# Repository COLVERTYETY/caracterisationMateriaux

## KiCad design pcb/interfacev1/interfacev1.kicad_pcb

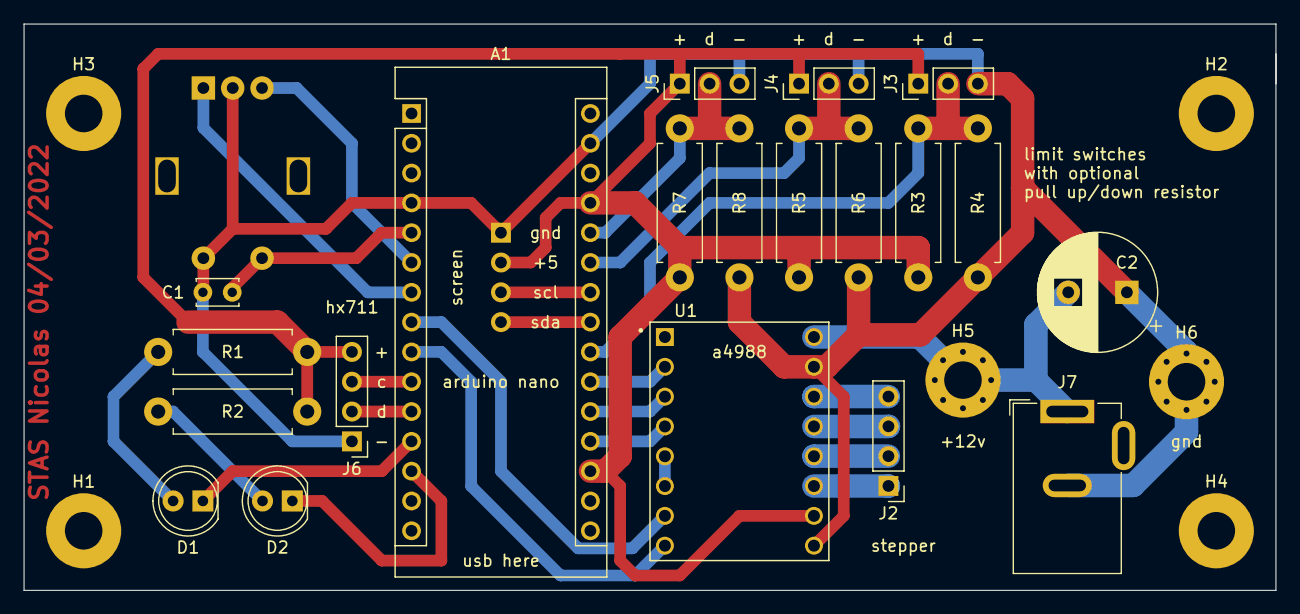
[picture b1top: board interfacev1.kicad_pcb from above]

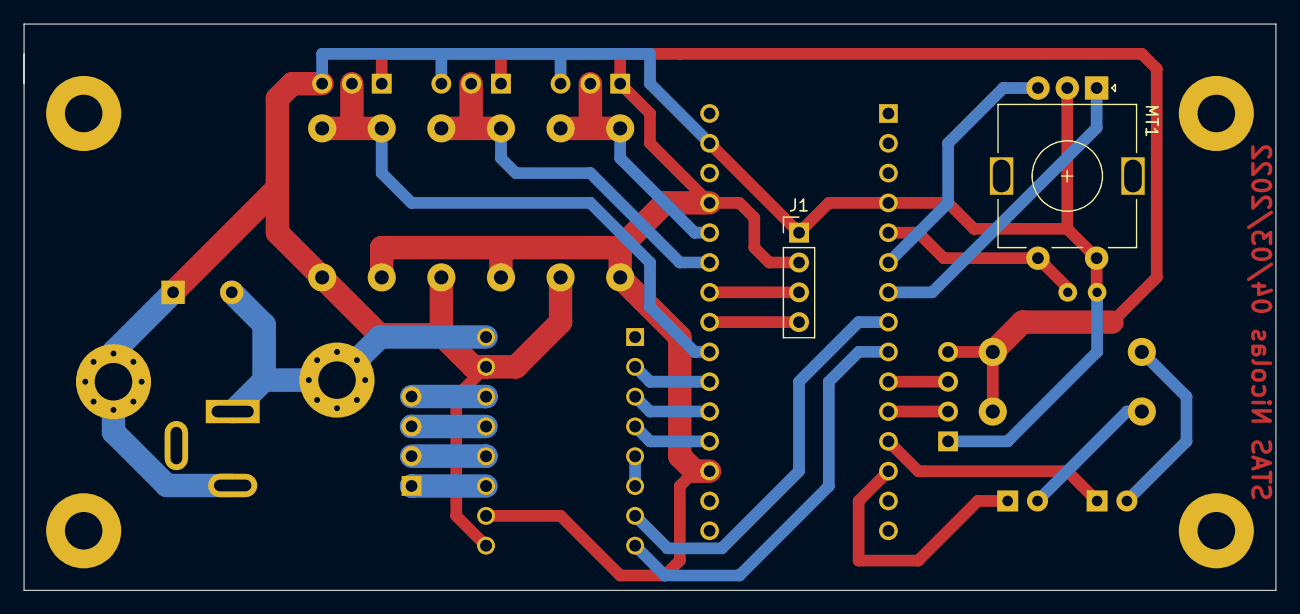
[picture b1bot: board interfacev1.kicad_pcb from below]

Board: 2 copper layers, 106.7 x 48.3 mm, 28 parts (2 on the bottom side), 27 nets.

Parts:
A1: Arduino_Nano_Every; Arduino_Nano
C1: C_Small; C_Disc_D3.4mm_W2.1mm_P2.50mm
C2: C; CP_Radial_D10.0mm_P5.00mm
D1, D2: LED; LED_D5.0mm
H1, H2, H3, H4: MountingHole; MountingHole_3.2mm_M3_Pad
H5, H6: MountingHole_Pad; MountingHole_3.2mm_M3_Pad_Via
J1, J2, J6: Conn_01x04_Female; PinHeader_1x04_P2.54mm_Vertical
J3, J4, J5: Conn_01x03_Female; PinHeader_1x03_P2.54mm_Vertical
J7: Jack-DC; BarrelJack_GCT_DCJ200-10-A_Horizontal
MT1: PEC11R-4215F-S0024; RotaryEncoder_Alps_EC11E-Switch_Vertical_H20mm
R1, R2, R3, R4, R5, R6, R7, R8: R; R_Axial_DIN0411_L9.9mm_D3.6mm_P12.70mm_Horizontal
U1: A4988_STEPPER_MOTOR_DRIVER_CARRIER; MODULE_A4988_STEPPER_MOTOR_DRIVER_CARRIER

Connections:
+5V: A1.18 (AREF), A1.27 (+5V), J1.2, J3.1, J4.1, J5.1, J6.4, R1.2, R2.2, R3.1, R5.1, R7.1, U1.10 (VDD)
+12V: C2.2, H5.1, J7.1, U1.16 (VMOT)
GND: A1.4 (GND), A1.29 (GND), C1.1, C2.1, H6.1, J1.1, J3.3, J4.3, J5.3, J6.1, J7.2, MT1.C, MT1.S2 (SHIELD), R4.2, R6.2, R8.2, U1.9 (GND), U1.15 (GND)
unnamed: A1.12 (D9), D1.1 (K)
unnamed: A1.13 (D10), D2.1 (K)
unnamed: D1.2 (A), R1.1
unnamed: D2.2 (A), R2.1
unnamed: J2.2, U1.12 (1A)
unnamed: J2.1, U1.11 (1B)
unnamed: J2.3, U1.13 (2A)
unnamed: J2.4, U1.14 (2B)
unnamed: U1.5 (~RESET), U1.6 (~SLEEP)
button: A1.5 (D2), C1.2, MT1.S1 (SHIELD)
dir: A1.9 (D6), U1.8 (DIR)
encod_dir: A1.7 (D4), MT1.A
encod_int: A1.6 (D3), MT1.B
l1: A1.22 (A3), J3.2, R3.2, R4.1
l2: A1.25 (A6), J4.2, R5.2, R6.1
l3: A1.26 (A7), J5.2, R7.2, R8.1
load_clk: A1.10 (D7), J6.3
load_data: A1.11 (D8), J6.2
ms1: A1.21 (A2), U1.2 (MS1)
ms2: A1.20 (A1), U1.3 (MS2)
ms3: A1.19 (A0), U1.4 (MS3)
scl: A1.24 (SCL/A5), J1.3
sda: A1.23 (SDA/A4), J1.4
step: A1.8 (D5), U1.7 (STEP)

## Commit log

2022-02-19 added stuff
